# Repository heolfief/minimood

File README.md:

# MiniMood

**[WORK IN PROGRESS]**

MiniMood is a digital and analog mono synth.
This is a 4th year degree school project at INSA Rennes, France leaded by a team of 4 students.

## Specs

* **USB powered**
* **USB MIDI** and **DIN (old school) MIDI**
* USB MIDI can be **device or host** **(direct plugging of a midi controller)**
* **3 voices polyphony**
* **ADSR filter**
* **3 oscillators** (sine, square, triangle, saw and arbitrary)
* **waveform editor** for arb oscillators
* **Detune control**
* **1 LFO** (sine, square, triangle, saw and arbitrary)
* **Analog low pass VCF**, control by potentiometer or **LFO**
* **Analog distortion**, same as Ibanez's Tube Screamer
* **Jack** headphones sound output
* Control by buttons, potentiometer and **2 OLED screens**
* **12 bits**, **44100Hz** sound output
* Based on STM32F446RE ARM microcontroller

## Software framework
This project firmware have been designed with the use of the [**STM32CubeIDE**](https://www.st.com/en/development-tools/stm32cubeide.html) on a Windows environment. To build source, open the .project file located in the Software/Firmware folder as a STM32CubeIDE project.

## LICENSING

Licence for this project is available in the LICENSE file.

**Notice of Non-Affiliation and Disclaimer :**

The name "MiniMood" is a tribute to the great and famous Minimoog synth. This is a school project and is not meant to be sold.

This project is  not affiliated, associated, authorized, endorsed by, or in any way officially connected with Moog Music Inc., or any of its subsidiaries or its affiliates. The official Moog Music Inc website can be found at https://www.moogmusic.com/.

The names Moog and Minimoog as well as related names, marks, emblems and images are registered trademarks of their respective owners.

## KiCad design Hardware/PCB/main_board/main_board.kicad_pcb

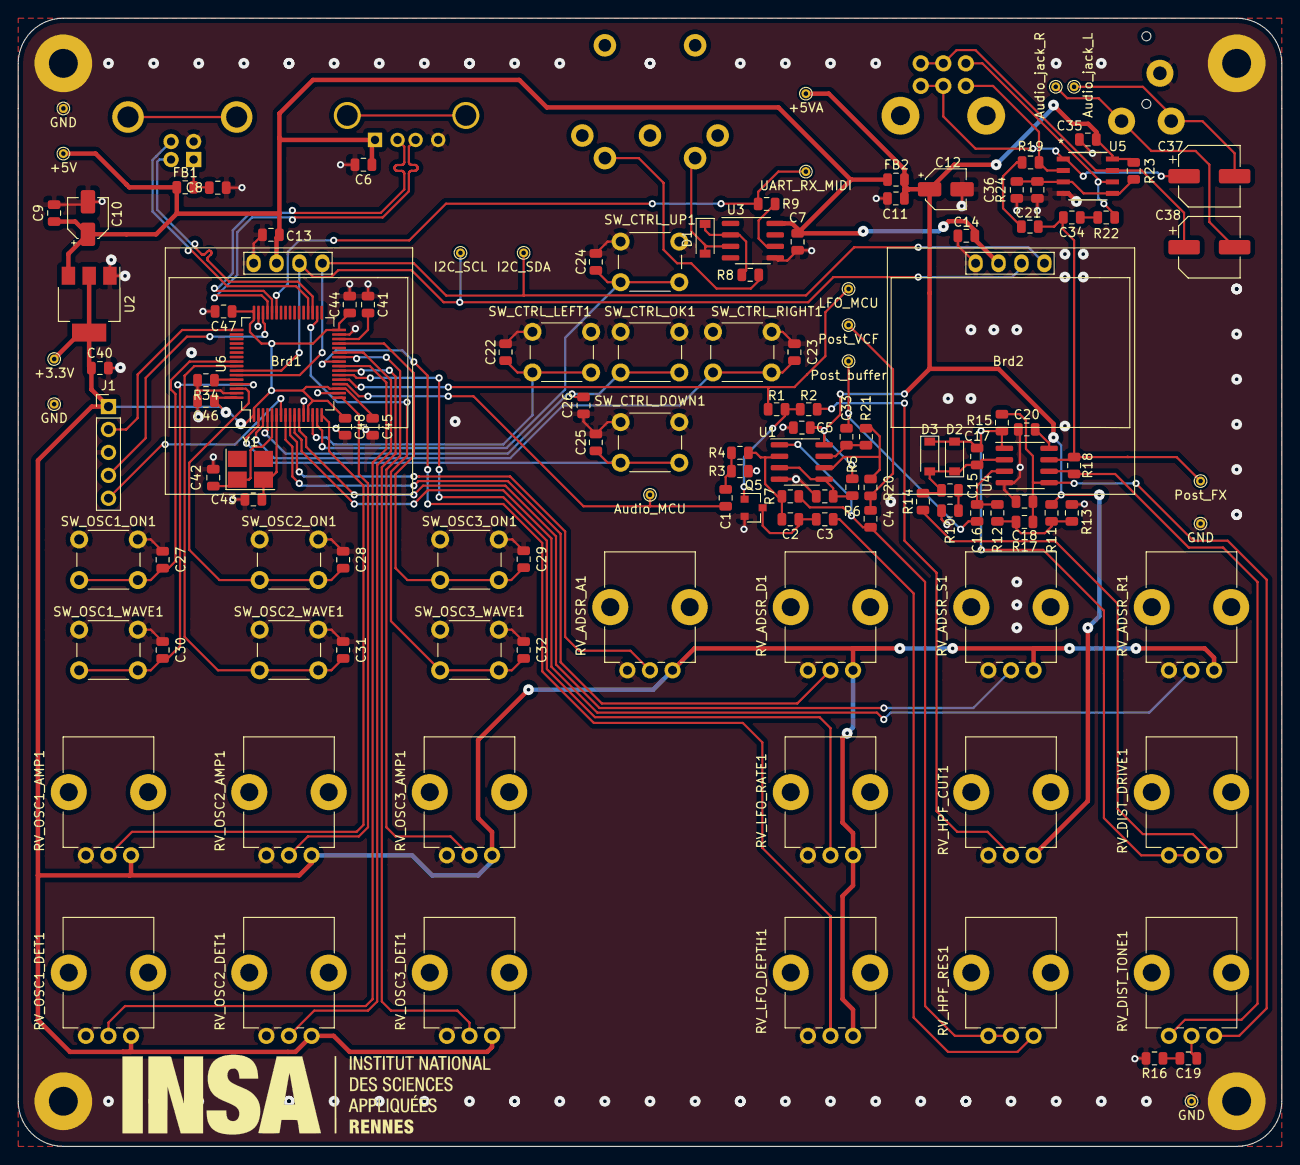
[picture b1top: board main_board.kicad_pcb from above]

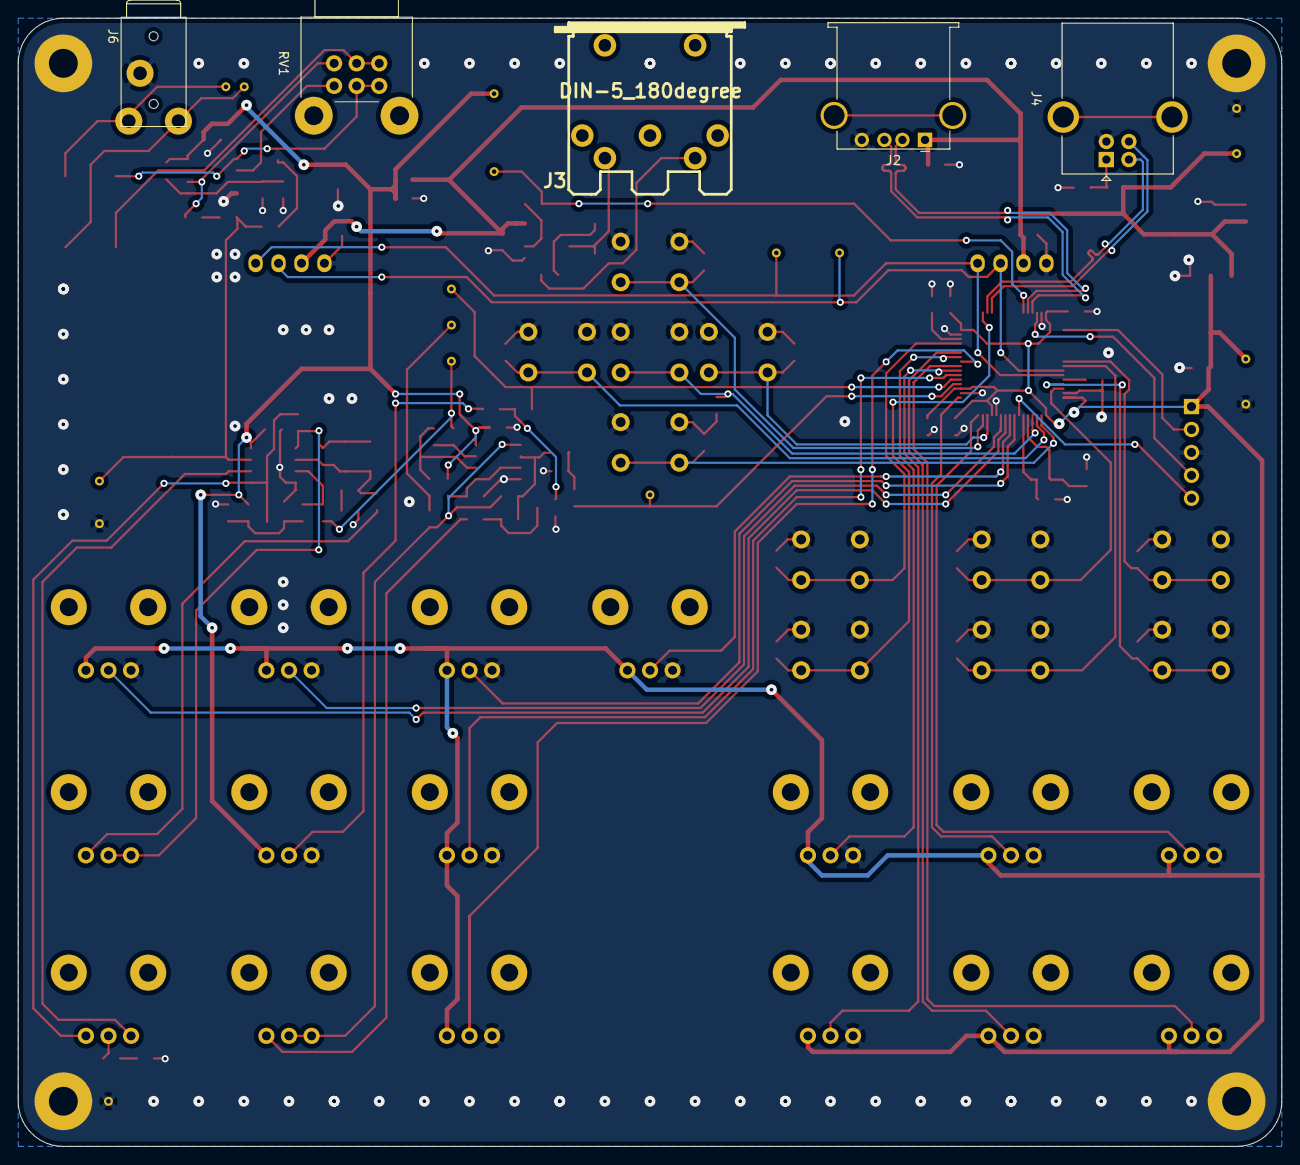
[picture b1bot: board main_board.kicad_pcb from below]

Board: 2 copper layers, 140.0 x 125.0 mm, 137 parts (5 on the bottom side), 80 nets.

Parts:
Brd1, Brd2: SSD1306; 128x64OLED
C1, C4: 4.7u; C_0805_2012Metric
C2, C3, C8: 10n; C_0805_2012Metric
C5, C6, C7, C9, C11, C13, C14, C20, C22, C23, C24, C25, C26, C27, C28, C29, C30, C31, C32, C33, C35, C40, C44, C45, C46, C47, C48: 100n; C_0805_2012Metric
C10, C12: 4.7u; CP_Elec_4x5.4
C15: 47p; C_0805_2012Metric
C16, C36: 1u; C_0805_2012Metric
C17: 51p; C_0805_2012Metric
C18, C19: 220n; C_0805_2012Metric
C21, C34: 2.2u; C_0805_2012Metric
C37, C38: 100u; CP_Elec_6.3x5.4
C41: 4.7uF (ESR<1ohm); C_0805_2012Metric
C42, C43: 20p; C_0805_2012Metric
D1: 1N4148; D_SOD-123
D2, D3: 1N4148W; D_SOD-123
FB1, FB2: BLM21PG221SH1D - Ferrite_Bead; L_0805_2012Metric
J1: SWD; PinHeader_1x05_P2.54mm_Vertical
J2: USB_A; USB_A_Stewart_SS-52100-001_Horizontal
J3: DIN-5_180degree; MIDI_DIN5
J4: USB_B; USB_B_OST_USB-B1HSxx_Horizontal
J5: I2C_SCL; TestPoint_THTPad_D1.0mm_Drill0.5mm
J6: AudioJack3; audio_jack_3.5mm_KYCON_STX-3000
J7, J8, J21, J22: GND; TestPoint_THTPad_D1.0mm_Drill0.5mm
J10: I2C_SDA; TestPoint_THTPad_D1.0mm_Drill0.5mm
J11: UART_RX_MIDI; TestPoint_THTPad_D1.0mm_Drill0.5mm
J12: Audio_jack_R; TestPoint_THTPad_D1.0mm_Drill0.5mm
J13: Audio_jack_L; TestPoint_THTPad_D1.0mm_Drill0.5mm
J14: +5V; TestPoint_THTPad_D1.0mm_Drill0.5mm
J15: Post_VCF; TestPoint_THTPad_D1.0mm_Drill0.5mm
J16: Post_buffer; TestPoint_THTPad_D1.0mm_Drill0.5mm
J17: Post_FX; TestPoint_THTPad_D1.0mm_Drill0.5mm
J19: Audio_MCU; TestPoint_THTPad_D1.0mm_Drill0.5mm
J20: LFO_MCU; TestPoint_THTPad_D1.0mm_Drill0.5mm
J23: +3.3V; TestPoint_THTPad_D1.0mm_Drill0.5mm
J24: +5VA; TestPoint_THTPad_D1.0mm_Drill0.5mm
Q5: BC847B; SOT-23
R1, R2, R9, R11, R12, R13, R17, R21, R34: 10k; R_0805_2012Metric
R3, R5, R6, R23, R24: 100k; R_0805_2012Metric
R4: 1M; R_0805_2012Metric
R7: 470k; R_0805_2012Metric
R8, R16: 220; R_0805_2012Metric
R10: 4.7k; R_0805_2012Metric
R14: 500; R_0805_2012Metric
R15, R18: 1k; R_0805_2012Metric
R19, R22: 8.2k; R_0805_2012Metric
R20: 3.9k; R_0805_2012Metric
RV1: 10k-dual-reverse-log; Potentiometer_Alps_RK09L_Double_Horizontal
RV_ADSR_A1: 10k; Potentiometer_Alps_RK09K_Single_Vertical
RV_ADSR_D1: 10k; Potentiometer_Alps_RK09K_Single_Vertical
RV_ADSR_R1: 10k; Potentiometer_Alps_RK09K_Single_Vertical
RV_ADSR_S1: 10k; Potentiometer_Alps_RK09K_Single_Vertical
RV_DIST_DRIVE1: 500k log; Potentiometer_Alps_RK09K_Single_Vertical
RV_DIST_TONE1: 22k; Potentiometer_Alps_RK09K_Single_Vertical
RV_HPF_CUT1: 10k; Potentiometer_Alps_RK09K_Single_Vertical
RV_HPF_RES1: 10k; Potentiometer_Alps_RK09K_Single_Vertical
RV_LFO_DEPTH1: 10k; Potentiometer_Alps_RK09K_Single_Vertical
RV_LFO_RATE1: 10k; Potentiometer_Alps_RK09K_Single_Vertical
RV_OSC1_AMP1, RV_OSC1_DET1, RV_OSC2_AMP1, RV_OSC2_DET1, RV_OSC3_AMP1, RV_OSC3_DET1: 10k; Potentiometer_Alps_RK09K_Single_Vertical
SW_CTRL_DOWN1: SW_Push; SW_PUSH_6mm_H13mm
SW_CTRL_LEFT1: SW_Push; SW_PUSH_6mm_H13mm
SW_CTRL_OK1: SW_Push; SW_PUSH_6mm_H13mm
SW_CTRL_RIGHT1: SW_Push; SW_PUSH_6mm_H13mm
SW_CTRL_UP1: SW_Push; SW_PUSH_6mm_H13mm
SW_OSC1_ON1, SW_OSC1_WAVE1, SW_OSC2_ON1, SW_OSC2_WAVE1, SW_OSC3_ON1, SW_OSC3_WAVE1: SW_Push; SW_PUSH_6mm_H13mm
U1: MCP6002-xSN; SOIC-8_3.9x4.9mm_P1.27mm
U2: LD1117S33TR_SOT223; SOT-223-3_TabPin2
U3: 6N137; SOIC-8_3.9x4.9mm_P1.27mm
U4: RC4558; SOIC-8_3.9x4.9mm_P1.27mm
U5: LM4808M_NOPB; LM4808M&slash_NOPB
U6: STM32F446RETx; LQFP-64_10x10mm_P0.5mm
Y1: Crystal; Crystal_SMD_3225-4Pin_3.2x2.5mm_HandSoldering

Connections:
+3V3: C40.1, C44.1, C45.1, C46.1, C47.1, C48.1, J1.1, J23.1, RV_ADSR_A1.1, RV_ADSR_D1.1, RV_ADSR_R1.1, RV_ADSR_S1.1, RV_LFO_DEPTH1.1, RV_LFO_RATE1.1, RV_OSC1_AMP1.1, RV_OSC1_DET1.1, RV_OSC2_AMP1.1, RV_OSC2_DET1.1, RV_OSC3_AMP1.1, RV_OSC3_DET1.1, U2.2, U6.1, U6.13, U6.19, U6.32, U6.48, U6.64
+5V: Brd1.2, Brd2.2, C6.1, C7.1, C9.1, C10.1, C13.1, C14.1, FB1.1, FB2.2, J2.1, J14.1, U2.3, U3.8
+5VA: C5.2, C11.1, C12.1, C20.2, C35.2, FB2.1, J24.1, R5.2, R11.1, R23.1, RV_HPF_CUT1.1, U1.8, U4.8, U5.8
/HMI/CTRL_DOWN: C25.1, SW_CTRL_DOWN1.2, U6.2
/HMI/CTRL_LEFT: C22.1, SW_CTRL_LEFT1.2, U6.14
/HMI/CTRL_OK: C26.1, SW_CTRL_OK1.2, U6.4
/HMI/CTRL_RIGHT: C23.1, SW_CTRL_RIGHT1.2, U6.3
/HMI/CTRL_UP: C24.1, SW_CTRL_UP1.2, U6.15
/HMI/I2C_display_SCL: Brd1.3, Brd2.3, J5.1, U6.58
/HMI/I2C_display_SDA: Brd1.4, Brd2.4, J10.1, U6.59
/MCU/ADC1_IN2: RV_OSC1_AMP1.2, U6.16
/MCU/ADC1_IN3: RV_OSC2_AMP1.2, U6.17
/MCU/ADC1_IN6: RV_LFO_RATE1.2, U6.22
/MCU/ADC1_IN7: RV_OSC3_DET1.2, U6.23
/MCU/ADC1_IN8: RV_OSC3_AMP1.2, U6.26
/MCU/ADC1_IN9: RV_OSC2_DET1.2, U6.27
/MCU/ADC1_IN10: RV_ADSR_D1.2, U6.8
/MCU/ADC1_IN11: RV_ADSR_A1.2, U6.9
/MCU/ADC1_IN12: RV_ADSR_R1.2, U6.10
/MCU/ADC1_IN13: RV_ADSR_S1.2, U6.11
/MCU/ADC1_IN14: RV_OSC1_DET1.2, U6.24
/MCU/ADC1_IN15: RV_LFO_DEPTH1.2, U6.25
/MCU/GPIO_PB4: C27.1, SW_OSC1_ON1.2, U6.56
/MCU/GPIO_PB5: C31.1, SW_OSC2_WAVE1.2, U6.57
/MCU/GPIO_PB8: C30.1, SW_OSC1_WAVE1.2, U6.61
/MCU/GPIO_PB9: C28.1, SW_OSC2_ON1.2, U6.62
/MCU/GPIO_PB10: C29.1, SW_OSC3_ON1.2, U6.29
/MCU/GPIO_PB13: C32.1, SW_OSC3_WAVE1.2, U6.34
/MCU/NRST: J1.5, U6.7
/MCU/SWCLK: J1.2, U6.49
/MCU/SWDIO: J1.4, U6.46
/MIDI/MIDI_Serial_RX: J11.1, R9.1, U6.43
/MIDI/MIDI_USB_D+: J2.3, U6.45
/MIDI/MIDI_USB_D-: J2.2, U6.44
/analogFX/2.5V_midpoint: R5.1, R6.1, U1.3, U1.5
/analogFX/AUDIO_IN: C1.2, J19.1, U6.20
/analogFX/CV_IN: J20.1, R1.2, U6.21
/analogFX/IN_DIST: C16.2, C33.1, J16.1
/analogFX/OUT_VCF: C4.1, J15.1, R20.2
/audio_out/AUDIO_IN: C21.1, C34.2, J17.1, R18.2, U4.7
/audio_out/Audio_jack_L: C37.2, J6.T, J13.1
/audio_out/Audio_jack_R: C38.2, J6.R, J12.1
/power/PWR_RAW: C8.1, FB1.2, J4.1
/power/USB_B_D+: J4.3, U6.36
/power/USB_B_D-: J4.2, U6.35
GND: Brd1.1, Brd2.1, C5.1, C6.2, C7.2, C8.2, C9.2, C10.2, C11.2, C12.2, C13.2, C14.2, C18.2, C20.1, C22.2, C23.2, C24.2, C25.2, C26.2, C27.2, C28.2, C29.2, C30.2, C31.2, C32.2, C35.1, C36.1, C40.2, C41.1, C42.1, C43.1, C44.2, C45.2, C46.2, C47.2, C48.2, J1.3, J2.4, J4.4, J6.S, J7.1, J8.1, J21.1, J22.1, Q5.2, R3.1, R6.2, R10.2, R13.1, R16.2, R24.2, R34.2, RV_ADSR_A1.3, RV_ADSR_D1.3, RV_ADSR_R1.3, RV_ADSR_S1.3, RV_HPF_CUT1.3, RV_LFO_DEPTH1.3, RV_LFO_RATE1.3, RV_OSC1_AMP1.3, RV_OSC1_DET1.3, RV_OSC2_AMP1.3, RV_OSC2_DET1.3, RV_OSC3_AMP1.3, RV_OSC3_DET1.3, SW_CTRL_DOWN1.1, SW_CTRL_LEFT1.1, SW_CTRL_OK1.1, SW_CTRL_RIGHT1.1, SW_CTRL_UP1.1, SW_OSC1_ON1.1, SW_OSC1_WAVE1.1, SW_OSC2_ON1.1, SW_OSC2_WAVE1.1, SW_OSC3_ON1.1, SW_OSC3_WAVE1.1, U1.4, U2.1, U3.5, U4.4, U5.4, U6.12, U6.18, U6.31, U6.47, U6.63
unnamed: C1.1, R3.2, R4.2
unnamed: C2.1, C3.2, Q5.3
unnamed: C2.2, R4.1, R7.2, U1.2
unnamed: C3.1, RV_HPF_RES1.1
unnamed: C4.2, R7.1, RV_HPF_RES1.2, RV_HPF_RES1.3, U1.1
unnamed: C15.1, C17.2, D2.1, D3.2, R14.2, U4.2
unnamed: C15.2, R10.1
unnamed: C16.1, R12.2, U4.3
unnamed: C17.1, D2.2, D3.1, R15.1, RV_DIST_DRIVE1.2, RV_DIST_DRIVE1.3, U4.1
unnamed: C18.1, R15.2, R17.1, RV_DIST_TONE1.1, U4.5
unnamed: C19.1, RV_DIST_TONE1.2
unnamed: C19.2, R16.1
unnamed: C21.2, R19.2
unnamed: C33.2, R21.1, U1.7
unnamed: C34.1, R22.1
unnamed: C36.2, R23.2, R24.1, U5.3, U5.5
unnamed: C37.1, RV1.4, RV1.5, U5.1
unnamed: C38.1, RV1.1, RV1.2, U5.7
unnamed: C41.2, U6.30
unnamed: C42.2, U6.5, Y1.1
unnamed: C43.2, U6.6, Y1.2
unnamed: D1.1, R8.1, U3.2
unnamed: D1.2, J3.4, U3.3
unnamed: J3.5, R8.2
unnamed: Q5.1, R1.1, R2.1
unnamed: R2.2, RV_HPF_CUT1.2
unnamed: R9.2, U3.6
unnamed: R11.2, R12.1, R13.2, R17.2
unnamed: R14.1, RV_DIST_DRIVE1.1
unnamed: R18.1, RV_DIST_TONE1.3, U4.6
unnamed: R19.1, RV1.6, U5.2
unnamed: R20.1, R21.2, U1.6
unnamed: R22.2, RV1.3, U5.6
unnamed: R34.1, U6.60

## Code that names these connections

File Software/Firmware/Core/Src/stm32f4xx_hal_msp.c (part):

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    __HAL_RCC_GPIOA_CLK_ENABLE();
    __HAL_RCC_GPIOB_CLK_ENABLE();
    /**ADC1 GPIO Configuration
    PC0     ------> ADC1_IN10
    PC1     ------> ADC1_IN11
    PC2     ------> ADC1_IN12
    PC3     ------> ADC1_IN13
    PA2     ------> ADC1_IN2
    PA3     ------> ADC1_IN3
    PA6     ------> ADC1_IN6
    PA7     ------> ADC1_IN7
    PC4     ------> ADC1_IN14
    PC5     ------> ADC1_IN15
    PB0     ------> ADC1_IN8
    PB1     ------> ADC1_IN9
    */
    GPIO_InitStruct.Pin = ADSR_D_Pin|ADSR_A_Pin|ADSR_R_Pin|ADSR_S_Pin
                          |OSC1_DET_Pin|LFO_DEPTH_Pin;
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    __HAL_RCC_ADC1_CLK_DISABLE();

    /**ADC1 GPIO Configuration
    PC0     ------> ADC1_IN10
    PC1     ------> ADC1_IN11
    PC2     ------> ADC1_IN12
    PC3     ------> ADC1_IN13
    PA2     ------> ADC1_IN2
    PA3     ------> ADC1_IN3
    PA6     ------> ADC1_IN6
    PA7     ------> ADC1_IN7
    PC4     ------> ADC1_IN14
    PC5     ------> ADC1_IN15
    PB0     ------> ADC1_IN8
    PB1     ------> ADC1_IN9
    */
    HAL_GPIO_DeInit(GPIOC, ADSR_D_Pin|ADSR_A_Pin|ADSR_R_Pin|ADSR_S_Pin
                          |OSC1_DET_Pin|LFO_DEPTH_Pin);
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
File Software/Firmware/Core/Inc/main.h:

/* USER CODE BEGIN Header */
/**
  ******************************************************************************
  * @file           : main.h
  * @brief          : Header for main.c file.
  *                   This file contains the common defines of the application.
  ******************************************************************************
  * @attention
  *
  * <h2><center>&copy; Copyright (c) 2020 STMicroelectronics.
  * All rights reserved.</center></h2>
  *
  * This software component is licensed by ST under BSD 3-Clause license,
  * the "License"; You may not use this file except in compliance with the
  * License. You may obtain a copy of the License at:
  *                        opensource.org/licenses/BSD-3-Clause
  *
  ******************************************************************************
  */
/* USER CODE END Header */

/* Define to prevent recursive inclusion -------------------------------------*/
#ifndef __MAIN_H
#define __MAIN_H

#ifdef __cplusplus
extern "C" {
#endif

/* Includes ------------------------------------------------------------------*/
#include "stm32f4xx_hal.h"

/* Private includes ----------------------------------------------------------*/
/* USER CODE BEGIN Includes */

/* USER CODE END Includes */

/* Exported types ------------------------------------------------------------*/
/* USER CODE BEGIN ET */

/* USER CODE END ET */

/* Exported constants --------------------------------------------------------*/
/* USER CODE BEGIN EC */

/* USER CODE END EC */

/* Exported macro ------------------------------------------------------------*/
/* USER CODE BEGIN EM */

/* USER CODE END EM */

/* Exported functions prototypes ---------------------------------------------*/
void Error_Handler(void);

/* USER CODE BEGIN EFP */

/* USER CODE END EFP */

/* Private defines -----------------------------------------------------------*/
#define CTRL_DOWN_Pin GPIO_PIN_13
#define CTRL_DOWN_GPIO_Port GPIOC
#define CTRL_RIGHT_Pin GPIO_PIN_14
#define CTRL_RIGHT_GPIO_Port GPIOC
#define CTRL_OK_Pin GPIO_PIN_15
#define CTRL_OK_GPIO_Port GPIOC
#define ADSR_D_Pin GPIO_PIN_0
#define ADSR_D_GPIO_Port GPIOC
#define ADSR_A_Pin GPIO_PIN_1
#define ADSR_A_GPIO_Port GPIOC
#define ADSR_R_Pin GPIO_PIN_2
#define ADSR_R_GPIO_Port GPIOC
#define ADSR_S_Pin GPIO_PIN_3
#define ADSR_S_GPIO_Port GPIOC
#define CTRL_LEFT_Pin GPIO_PIN_0
#define CTRL_LEFT_GPIO_Port GPIOA
#define CTRL_UP_Pin GPIO_PIN_1
#define CTRL_UP_GPIO_Port GPIOA
#define OSC1_AMP_Pin GPIO_PIN_2
#define OSC1_AMP_GPIO_Port GPIOA
#define OSC2_AMP_Pin GPIO_PIN_3
#define OSC2_AMP_GPIO_Port GPIOA
#define AUDIO_OUT_Pin GPIO_PIN_4
#define AUDIO_OUT_GPIO_Port GPIOA
#define LFO_CV_OUT_Pin GPIO_PIN_5
#define LFO_CV_OUT_GPIO_Port GPIOA
#define LFO_RATE_Pin GPIO_PIN_6
#define LFO_RATE_GPIO_Port GPIOA
#define OSC3_DET_Pin GPIO_PIN_7
#define OSC3_DET_GPIO_Port GPIOA
#define OSC1_DET_Pin GPIO_PIN_4
#define OSC1_DET_GPIO_Port GPIOC
#define LFO_DEPTH_Pin GPIO_PIN_5
#define LFO_DEPTH_GPIO_Port GPIOC
#define OSC3_AMP_Pin GPIO_PIN_0
#define OSC3_AMP_GPIO_Port GPIOB
#define OSC2_DET_Pin GPIO_PIN_1
#define OSC2_DET_GPIO_Port GPIOB
#define OSC3_ON_Pin GPIO_PIN_10
#define OSC3_ON_GPIO_Port GPIOB
#define OSC3_WAVE_Pin GPIO_PIN_13
#define OSC3_WAVE_GPIO_Port GPIOB
#define OSC1_ON_Pin GPIO_PIN_4
#define OSC1_ON_GPIO_Port GPIOB
#define OSC2_WAVE_Pin GPIO_PIN_5
#define OSC2_WAVE_GPIO_Port GPIOB
#define OSC1_WAVE_Pin GPIO_PIN_8
#define OSC1_WAVE_GPIO_Port GPIOB
#define OSC2_ON_Pin GPIO_PIN_9
#define OSC2_ON_GPIO_Port GPIOB
/* USER CODE BEGIN Private defines */

/* USER CODE END Private defines */

#ifdef __cplusplus
}
#endif

#endif /* __MAIN_H */

/************************ (C) COPYRIGHT STMicroelectronics *****END OF FILE****/

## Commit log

2020-01-31 New folders
    Place holders for new folders added. To separate Hardware from Software
2020-02-14 Add firmware base project structure and audio core
2020-02-15 Code and folders structure cleanup
2020-02-15 Code cleanup and ADSR struct implementation
2020-02-15 ADSR and Note implementation
2020-02-16 Finish note implementation
2020-02-16 Format code
2020-02-16 Polyphony implementation
2020-02-16 Add sys param and high level note on/off functions
2020-02-16 Add test code
2020-02-17 Debug polyphony
2020-02-18 creating the display branch
2020-02-18 Adding the files previously worked on
2020-02-18 adapting the project settings
    no more compile errors, sorry
2020-02-19 ADSR display frame
2020-02-19 Change LUT to be without offset
2020-02-19 Remove float cast
2020-02-19 Add LUT calculator file
2020-02-19 Fix constant volume issue
2020-02-19 value update of ADSR
2020-02-20 Add simulation files for VCF
2020-02-20 Activate DAC2 output, remove test GPIO
2020-02-20 Init DAC2
2020-02-20 Implement LFO
2020-02-20 Add VCF shematics (KiCad)
2020-02-21 Debug LFO
2020-02-21 Add optimization to GCC
2020-02-21 Add KiCad gitignore
2020-02-21 Remove unused files
2020-02-21 Add PCB module for VCF
2020-02-21 Add NUCLEO footprint
2020-02-22 Add programming connector to PCB
2020-02-22 Add MIDI hardware
2020-02-22 Add power supply schematics and layout
2020-02-22 Add missing power connection
2020-02-23 Add OLED screen to PCB
2020-02-23 Add HMI buttons and pots to PCB
2020-02-23 Place HMI
2020-02-23 Place connectors
2020-02-25 configure cubeMX for usb host
2020-02-25 add library and test for this library
2020-02-25 Flip connectors, add 3D models
2020-02-25 add midi_application.h and midi_application.c
2020-02-25 add struct midi Message
2020-02-25 Add simulation file for Distortion
2020-02-25 Place VCF components, I2C bus
2020-02-25 Add output buffer to VCF
2020-02-25 OSC frames added
2020-02-25 Update 3D view
2020-02-25 fix a bug on MidiMessage
2020-02-26 setting the merge and updating osc display
2020-02-26 Route GPIO
2020-02-26 Route PWR
2020-02-27 Cleanup routing
2020-02-29 Start ADC config
2020-03-01 Change GPIO config
2020-03-01 Label GPIO, create HMI files
2020-03-01 Add debounce capacitors
2020-03-02 Implement low-level software button debounce
2020-03-02 Fix pointer bug
2020-03-02 Change debounce mechanism to detect falling edges
2020-03-02 Implement process buttons : OSC ON
2020-03-02 Finish implementation of osc buttons
2020-03-03 start to implement pots value mapping
2020-03-03 Add Tim7 IT routine for HMI
2020-03-03 adding bitmap waves
2020-03-04 Change core frequency
2020-03-04 Change HMI Tim7 IT frequency according to new core freq
2020-03-04 Update LUT values fo new core freq
2020-03-05 Add return statement on what parameters changed (HMI)
2020-03-05 updating sin bmp / renamed file sin.h
2020-03-05 adding all the waveforms bmp needed
2020-03-05 Fix debounce bug
2020-03-06 correcting waveforms position / add selection of oscillos
2020-03-07 Improved ADSR display change
2020-03-08 Add capacitor to the output buffer Change capacitor value to the Tone/Volume stage Remove output resistor from the VCF Change resistor value of the output buffer
2020-03-08 Modify distortion components
2020-03-08 Add the output adaptation
2020-03-15 Adds Arb editor screen
    change of values untested, but selection works
2020-03-21 add the LFO screens and optimizes arb editor
2020-03-21 Add FX buffer and headphone amp to schematics
2020-03-21 Route PCB changes
2020-03-21 Float frequency visual added
2020-03-22 Replace diode by transistor and change the reference to 547B 557B
2020-03-24 Fix GND via
2020-03-26 Fix DRC issue
2020-03-26 Add test points headers
2020-03-29 Clean folder
2020-09-08 Use bare STM32 instead of nucleo board. Schematics update
2020-09-12 Re-layout HMI, pre route
2020-09-13 add midi device USB
2020-09-13 Finish PCB routing
2020-09-23 Use headphone amp IC instead of discrete amp
2020-09-24 Fix HMI timer frequency to be exactly 50Hz
2020-09-24 Optimize interrupts, use proper callbacks
2020-09-24 Junk folders cleanup
2020-09-24 Remove user specific file
2020-09-24 Add I2C module to CubeMX to prepare Display_implement merge
2020-09-24 Update readme to add WIP warning
2020-09-24 Update readme specs
2020-09-24 Add Doxyfile
2020-09-24 Migrate project to CubeMX 6.0.1
2020-09-25 Change discrete defines to enums
2020-09-25 Code formating
2020-09-25 Folder structure and includes cleanup
2020-09-25 Change functions names to specify they are related to display not audio
2020-09-26 Implement displays FSM code structure
2020-09-27 Add main screens to FSM
2020-09-28 Configure USB clock for future merge
2020-09-28 Change NVIC priorities
2020-09-29 Proper implementation of dual screen feature
2020-10-01 Re-implement OSC drawing functions
2020-10-02 Re-implement LFO drawing functions
2020-10-04 Fix sampling rate constant set to wrong value
2020-10-05 Re-implement ADSR drawing functions
2020-10-06 Improve ADSR axis drawing
2020-10-06 Add doxygen
2020-10-08 Display LFO as an oscilloscope
2020-10-08 Add LFO display data interpolation
2020-10-08 Cleanup unused timer

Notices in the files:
parts and their libraries:
Copyright 2016 Accelerated Designs. All rights reserved.
